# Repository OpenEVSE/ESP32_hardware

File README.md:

# ESP32_hardware
OpenEVSE network communications controllers based on the ESP32 Module.

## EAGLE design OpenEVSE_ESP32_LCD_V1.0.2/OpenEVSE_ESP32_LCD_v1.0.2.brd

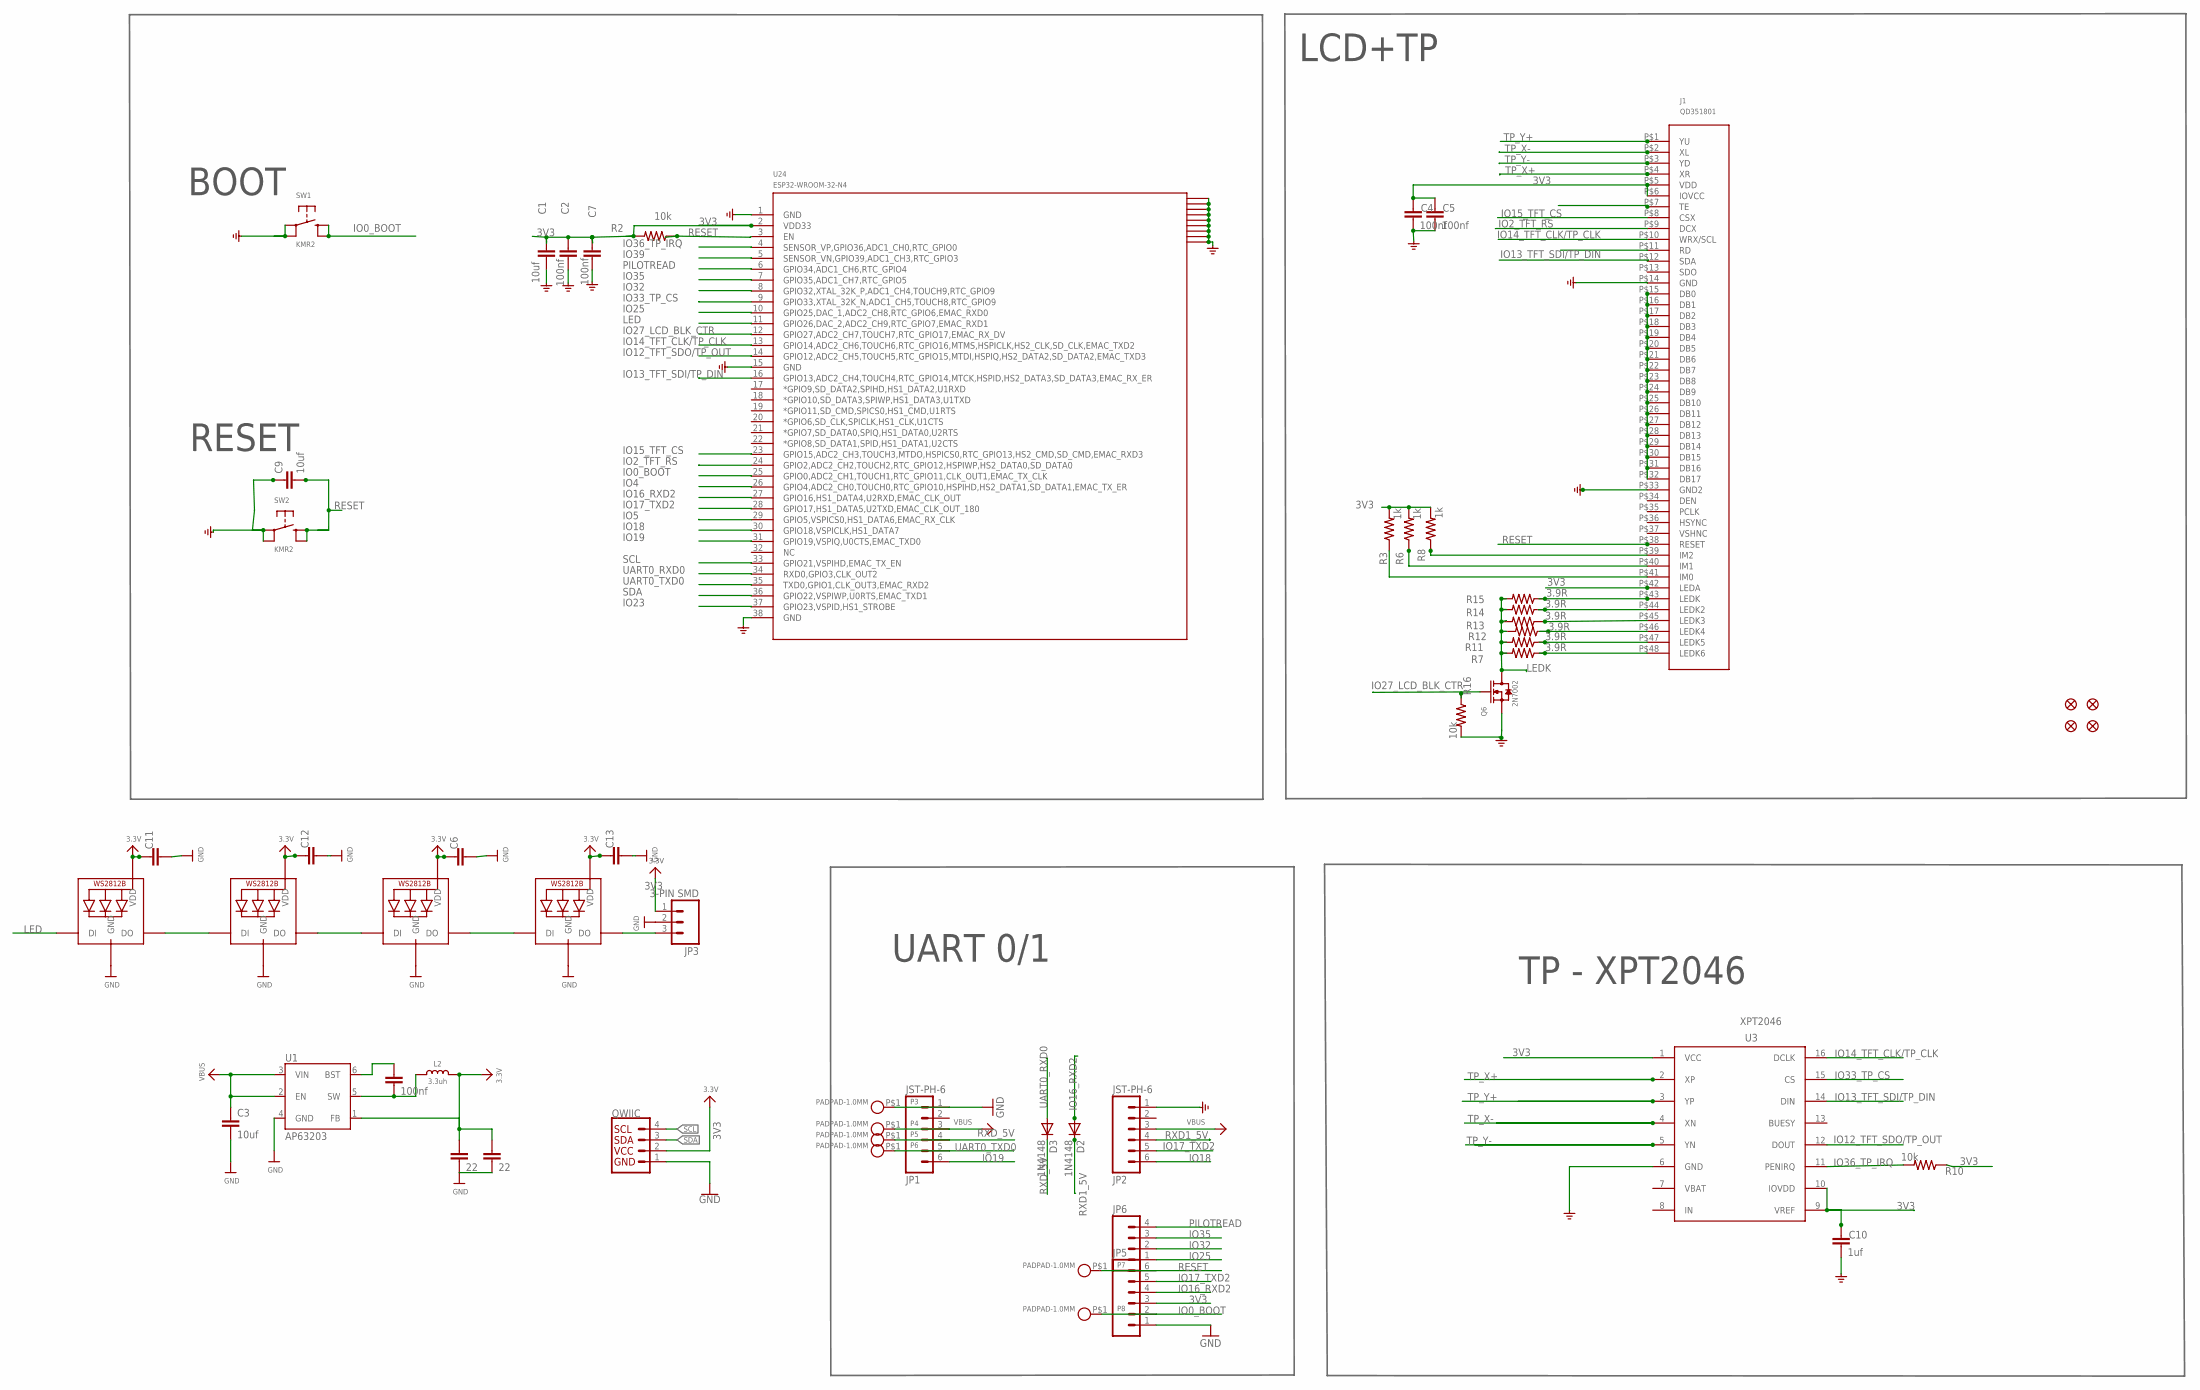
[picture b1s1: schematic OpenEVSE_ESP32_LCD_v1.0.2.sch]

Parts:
C1, C3, C9: 10uf; 0805
C2, C4, C5, C7, C14: 100nf; 0805
C6, C11, C12, C13: CAP0805; 0805
C8, C15: 22; 0805
C10: 1uf; 0805
D2, D3: 1N4148; SOD123
FID1, FID2, FID3, FID4: FIDUCIAL1X2.5; FIDUCIAL-1X2.5
J1: QD351801; QD351801-0.8MM*48
JP1, JP2: JST-PH-6
JP3: 3-PIN SMD; JST-3-SMD
JP5: M06SMD; 1X06-SMD
JP6: M04SMD; 1X04-SMD
L2: 3.3uh; MICROBUILDER_INDUCTOR_5X5MM_NR5040_NOTHERMALS
LED1, LED2, LED3, LED4: WS2812B3535; LED3535
P3, P4, P5, P6, P7, P8: PADPAD-1.0MM; PAD-1.0MM
Q6: 2N7002; SOT23
QWIIC: QWIIC_CONNECTORJS-1MM; JST04_1MM_RA
R2, R10, R16: 10k; 0805
R3, R6, R8: 1k; 0805
R7, R11, R12, R13, R14, R15: 3.9R; 0805
SW1, SW2: KMR2; BTN_KMR2_4.6X2.8
U1: AP63203; SOT23-6
U3: XP2046; XP2046-SSOP16
U24: ESP32-WROOM-32-N4

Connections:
3V3: C1.1, C2.1, C4.1, C5.1, C6.1, C7.1, C8.1, C10.1, C11.1, C12.1, C13.1, C15.1, J1.P$5 (VDD), J1.P$6 (IOVCC), J1.P$42 (LEDA), JP3.1, JP5.3, L2.P$2 (2), LED1.2 (VDD), LED2.2 (VDD), LED3.2 (VDD), LED4.2 (VDD), QWIIC.2, R2.2, R3.2, R6.2, R8.2, R10.1, U1.1 (FB), U3.1 (VCC), U3.9 (VREF), U3.10 (IOVDD), U24.2 (VDD33)
GND: C1.2, C2.2, C3.2, C4.2, C5.2, C6.2, C7.2, C8.2, C9.1, C10.2, C11.2, C12.2, C13.2, C15.2, J1.P$14 (GND), J1.P$33 (GND2), JP1.1, JP2.1, JP3.2, JP5.1, LED1.4 (GND), LED2.4 (GND), LED3.4 (GND), LED4.4 (GND), P3.P$1, Q6.2 (S), QWIIC.1, R16.2, SW1.A, SW1.A' (P1), SW2.A, SW2.A' (P1), U1.4 (GND), U3.6 (GND), U24.1 (GND), U24.15 (GND), U24.38 (GND), U24.41 (GND), U24.42 (GND), U24.43 (GND), U24.44 (GND), U24.45 (GND), U24.46 (GND), U24.47 (GND), U24.48 (GND), U24.49 (GND)
IO0_BOOT: JP5.2, P8.P$1, SW1.B (S), SW1.B' (S1), U24.25 (GPIO0,ADC2_CH1,TOUCH1,RTC_GPIO11,CLK_OU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)
IO2_TFT_RS: J1.P$9 (DCX), U24.24 (GPIO2,ADC2_CH2,TOUCH2,RTC_GPIO12,HSPIWP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)
IO4: U24.26 (GPIO4,ADC2_CH0,TOUCH0,RTC_GPIO10,HSPIHD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)
IO5: U24.29 (GPIO5,VSPICS0,HS1_DATA6,EMAC_RX_CLK)
IO12_TFT_SDO/TP_OUT: U3.12 (DOUT), U24.14 (GPIO12,ADC2_CH5,TOUCH5,RTC_GPIO15,MTDI,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)
IO13_TFT_SDI/TP_DIN: J1.P$12 (SDA), U3.14 (DIN), U24.16 (GPIO13,ADC2_CH4,TOUCH4,RTC_GPIO14,MTCK,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)
IO14_TFT_CLK/TP_CLK: J1.P$10 (WRX/SCL), U3.16 (DCLK), U24.13 (GPIO14,ADC2_CH6,TOUCH6,RTC_GPIO16,MTMS,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)
IO15_TFT_CS: J1.P$8 (CSX), U24.23 (GPIO15,ADC2_CH3,TOUCH3,MTDO,HSPICS0,RTC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)
IO16_RXD2: D2.A, JP5.4, U24.27 (GPIO16,HS1_DATA4,U2RXD,EMAC_CLK_OUT)
IO17_TXD2: JP2.5, JP5.5, U24.28 (GPIO17,HS1_DATA5,U2TXD,EMAC_CLK_OUT_180)
IO18: JP2.6, U24.30 (GPIO18,VSPICLK,HS1_DATA7)
IO19: JP1.6, U24.31 (GPIO19,VSPIQ,U0CTS,EMAC_TXD0)
IO23: U24.37 (GPIO23,VSPID,HS1_STROBE)
IO25: JP6.1, U24.10 (GPIO25,DAC_1,ADC2_CH8,RTC_GPIO6,EMAC_RX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)
IO27_LCD_BLK_CTR: Q6.1 (G), R16.1, U24.12 (GPIO27,ADC2_CH7,TOUCH7,RTC_GPIO17,EMAC_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)
IO32: JP6.2, U24.8 (GPIO32,XTAL_32K_P,ADC1_CH4,TOUCH9,RTC_G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)
IO33_TP_CS: U3.15 (CS), U24.9 (GPIO33,XTAL_32K_N,ADC1_CH5,TOUCH8,RTC_G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)
IO35: JP6.3, U24.7 (GPIO35,ADC1_CH7,RTC_GPIO5)
IO36_TP_IRQ: R10.2, U3.11 (PENIRQ), U24.4 (SENSOR_VP,GPIO36,ADC1_CH0,RTC_GPIO0)
IO39: U24.5 (SENSOR_VN,GPIO39,ADC1_CH3,RTC_GPIO3)
LED: LED1.1 (DI), U24.11 (GPIO26,DAC_2,ADC2_CH9,RTC_GPIO7,EMAC_RX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)
LEDK: Q6.3 (D), R7.2, R11.2, R12.2, R13.2, R14.2, R15.2
unnamed: LED1.3 (DO), LED2.1 (DI)
unnamed: J1.P$15 (DB0), J1.P$16 (DB1), J1.P$17 (DB2), J1.P$18 (DB3), J1.P$19 (DB4), J1.P$20 (DB5), J1.P$21 (DB6), J1.P$22 (DB7), J1.P$23 (DB8), J1.P$24 (DB9), J1.P$25 (DB10), J1.P$26 (DB11), J1.P$27 (DB12), J1.P$28 (DB13), J1.P$29 (DB14), J1.P$30 (DB15), J1.P$31 (DB16), J1.P$32 (DB17)
unnamed: LED3.3 (DO), LED4.1 (DI)
unnamed: C14.2, L2.P$1 (1), U1.5 (SW)
unnamed: J1.P$44 (LEDK2), R14.1
unnamed: LED2.3 (DO), LED3.1 (DI)
unnamed: J1.P$43 (LEDK), R15.1
unnamed: JP3.3, LED4.3 (DO)
unnamed: J1.P$39 (IM2), R8.1
unnamed: J1.P$40 (IM1), R6.1
unnamed: J1.P$41 (IM0), R3.1
unnamed: C14.1, U1.6 (BST)
unnamed: J1.P$45 (LEDK3), R13.1
unnamed: J1.P$46 (LEDK4), R12.1
unnamed: J1.P$47 (LEDK5), R11.1
unnamed: J1.P$48 (LEDK6), R7.1
PILOTREAD: JP6.4, U24.6 (GPIO34,ADC1_CH6,RTC_GPIO4)
RESET: C9.2, J1.P$38 (RESET), JP5.6, P7.P$1, R2.1, SW2.B (S), SW2.B' (S1), U24.3 (EN)
RXD1_5V: D2.C, JP2.4
RXD_5V: D3.C, JP1.4, P5.P$1
SCL: QWIIC.4, U24.33 (GPIO21,VSPIHD,EMAC_TX_EN)
SDA: QWIIC.3, U24.36 (GPIO22,VSPIWP,U0RTS,EMAC_TXD1)
TP_X+: J1.P$4 (XR), U3.2 (XP)
TP_X-: J1.P$2 (XL), U3.4 (XN)
TP_Y+: J1.P$1 (YU), U3.3 (YP)
TP_Y-: J1.P$3 (YD), U3.5 (YN)
UART0_RXD0: D3.A, U24.34 (RXD0,GPIO3,CLK_OUT2)
UART0_TXD0: JP1.5, P6.P$1, U24.35 (TXD0,GPIO1,CLK_OUT3,EMAC_RXD2)
VBUS: C3.1, JP1.3, JP2.3, P4.P$1, U1.2 (EN), U1.3 (VIN)

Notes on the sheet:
UART 0/1
BOOT
RESET
LCD+TP
TP - XPT2046

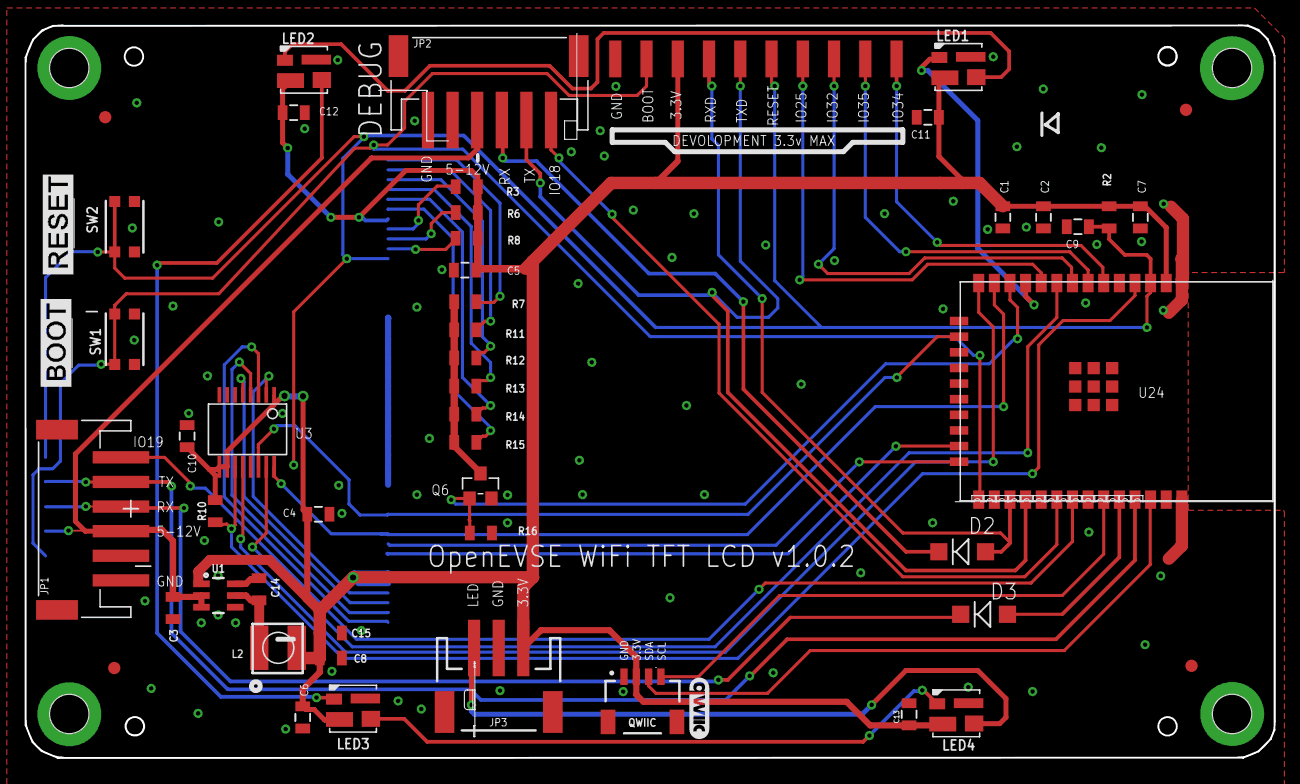
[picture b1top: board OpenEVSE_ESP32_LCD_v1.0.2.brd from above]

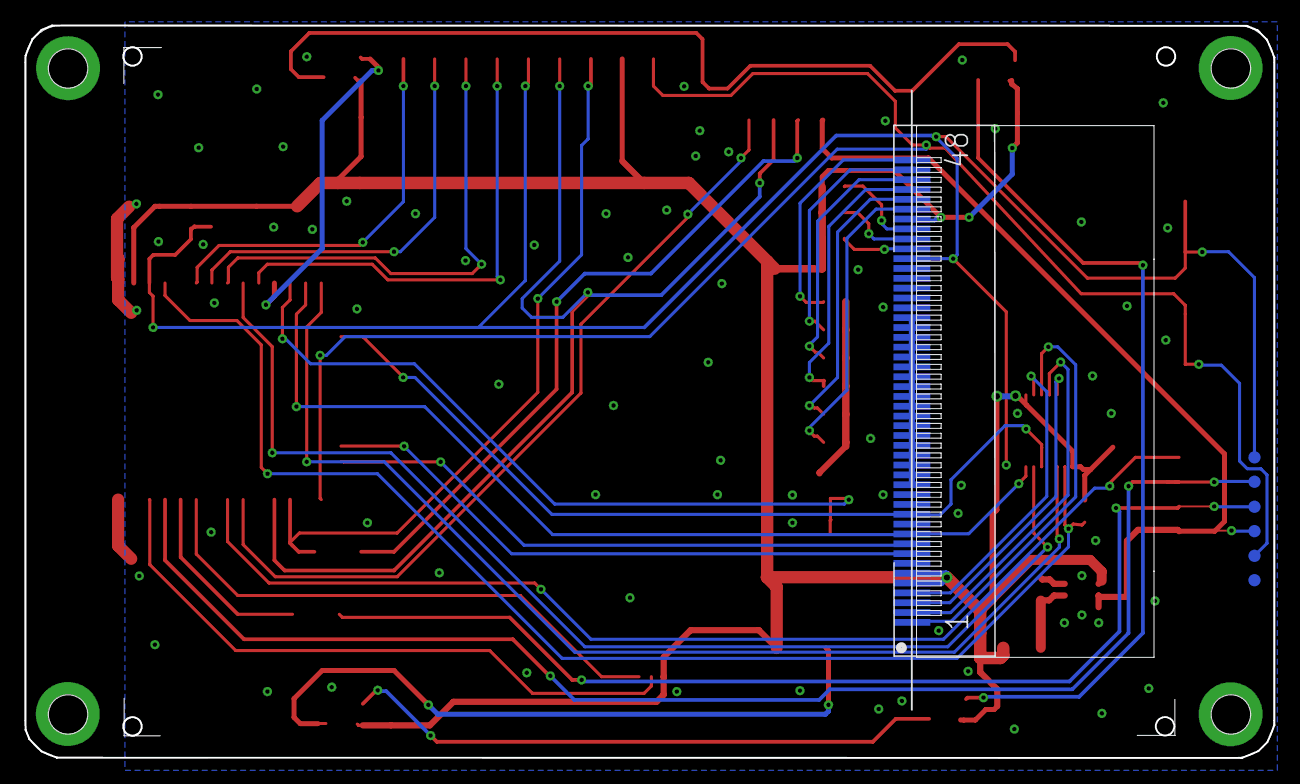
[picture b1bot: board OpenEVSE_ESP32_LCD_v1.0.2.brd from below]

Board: 2 copper layers, 101.5 x 59.5 mm, 59 parts (7 on the bottom side), 49 nets.

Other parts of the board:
U$2: 3.5底板框
U$44: QWIIC_5MM

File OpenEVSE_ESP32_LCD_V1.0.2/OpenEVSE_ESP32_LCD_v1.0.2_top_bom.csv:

Comment,Designator,Footprint,LCSC Part #
1N4148,C6 C11 C12 C13 JP5 JP6 QWIIC D2 D3,SOD123,
1k,R3 R6 R8,0805,
1uf,C10,0805,
2N7002,Q6,SOT23,
3-PIN SMD,JP3,JST-3-SMD,
3.3uh,L2,MICROBUILDER_INDUCTOR_5X5MM_NR5040_NOTHERMALS,
3.9R,R7 R11 R12 R13 R14 R15,0805,
4.7uf,C9,0805,
10k,R2 R10 R16,0805,
10uf,C1 C3,0805,
22,C8 C15,0805,
100nf,C2 C4 C5 C7 C14,0805,
AP63203,U1,SOT23-6,
ESP32-WROOM-32-N4,U24,ESP32-WROOM-32-N4,
FIDUCIAL1X2.5,FID1 FID2 FID3 FID4,FIDUCIAL-1X2.5,
JST-PH-6,JP1 JP2,JST-PH-6,
KMR2,SW1 SW2,BTN_KMR2_4.6X2.8,
WS2812B3535,LED1 LED2 LED3 LED4,LED3535,
XP2046,U3,XP2046-SSOP16,

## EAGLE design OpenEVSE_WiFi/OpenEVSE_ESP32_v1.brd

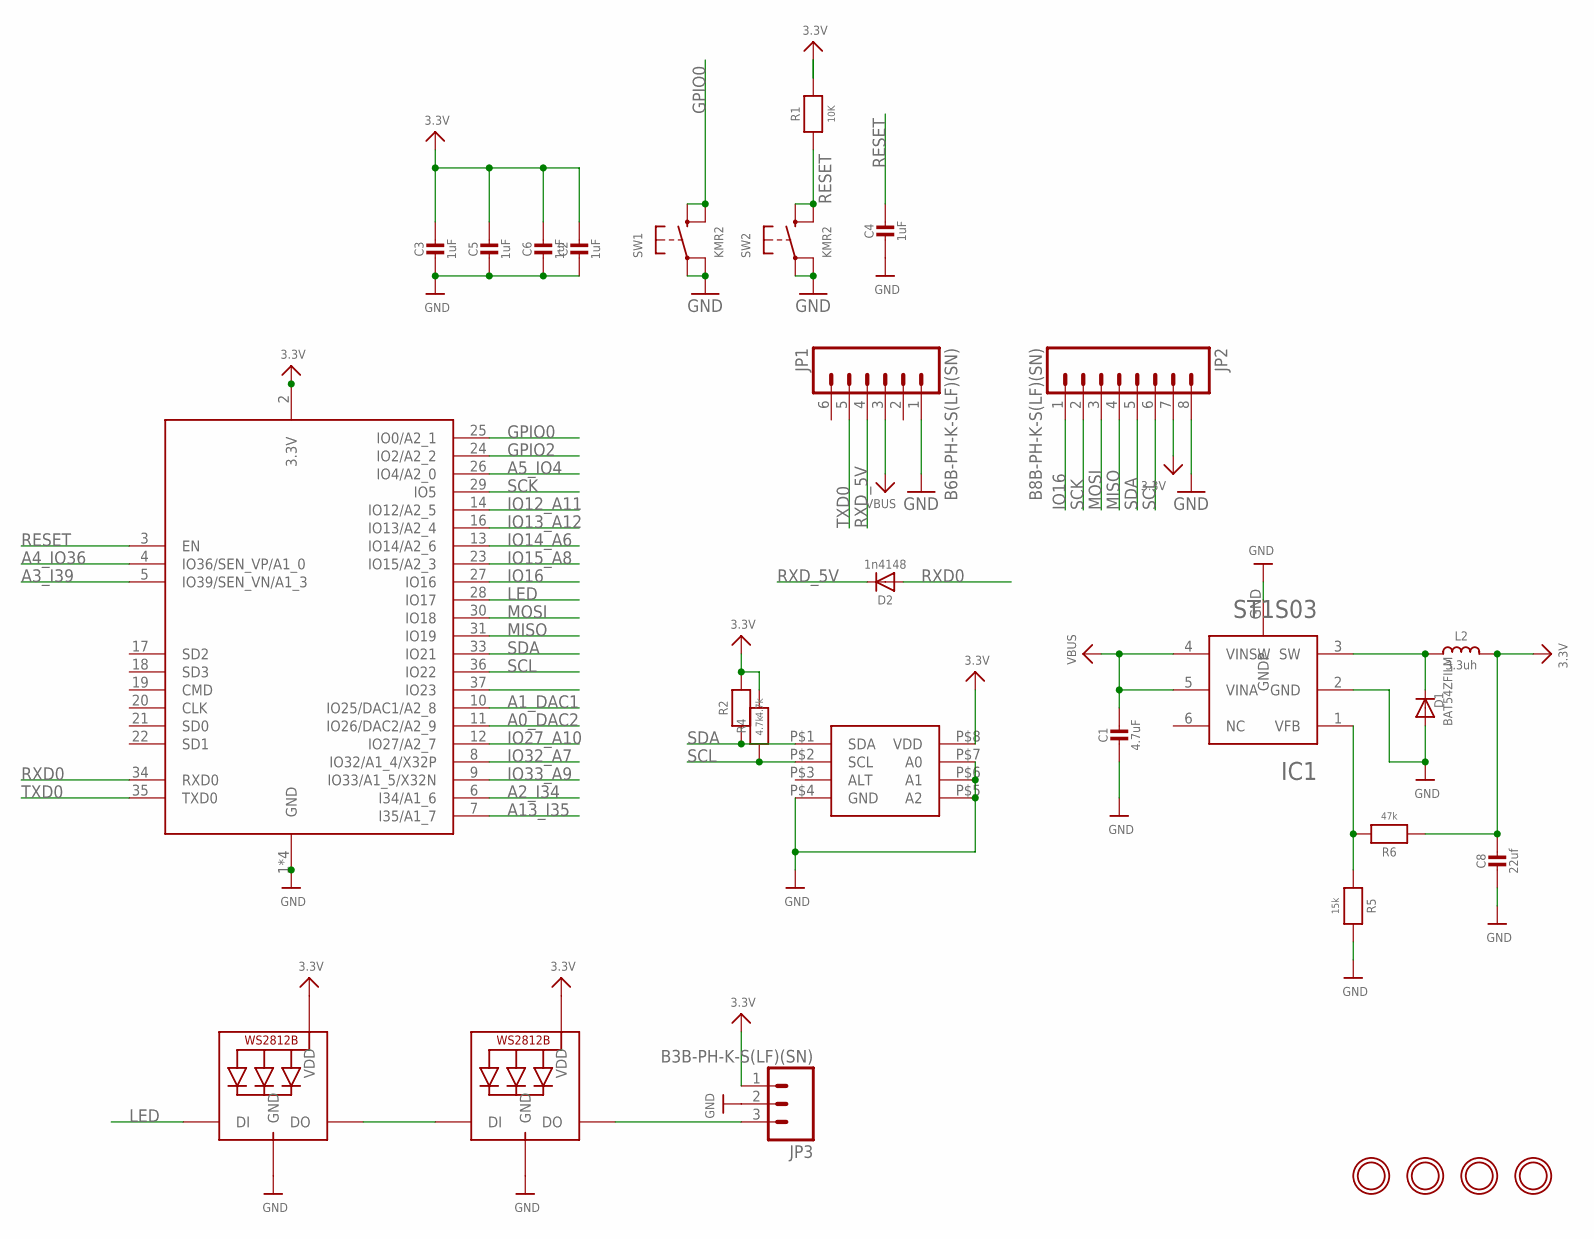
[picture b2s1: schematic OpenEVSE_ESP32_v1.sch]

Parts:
C1: 4.7uF; 0603-NO
C2, C3, C4, C5, C6: 1uF; 0603-NO
C8: 22uf; 0603-NO
D1: BAT54ZFILM; SOD-123
D2: 1n4148; SOD-323
IC1: ST1S03; DFQN6D
IC2: MCP9808; MSOP8
JP1: B6B-PH-K-S(LF)(SN); JST6
JP2: B8B-PH-K-S(LF)(SN); JST8
JP3: B3B-PH-K-S(LF)(SN); JST-3-PTH-VERT
L2: 3.3uh; MICROBUILDER_INDUCTOR_5X5MM_NR5040_NOTHERMALS
LED1, LED2: SK6812MINI; MICROBUILDER_LED3535
R1: 10K; 0603-NO
R2, R4: 4.7k; 0603-NO
R5: 15k; 0603-NO
R6: 47k; 0603-NO
SW1, SW2: KMR2; BTN_KMR2_4.6X2.8
U$8, U$17, U$25, U$27: MOUNTINGHOLE2.5; MOUNTINGHOLE_2.5_PLATED
X2: ESP32-WROOM-32; WROOM32_SKINNY

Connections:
3.3V: C2.1, C3.1, C5.1, C6.1, C8.1, IC2.P$8 (VDD), JP2.7, JP3.1, L2.P$2 (2), LED1.2 (VDD), LED2.2 (VDD), R1.2, R2.2, R4.2, R6.1, X2.2 (3.3V)
A0_DAC2: X2.11 (IO26/DAC2/A2_9)
A1_DAC1: X2.10 (IO25/DAC1/A2_8)
A2_I34: X2.6 (I34/A1_6)
A3_I39: X2.5 (IO39/SEN_VN/A1_3)
A4_IO36: X2.4 (IO36/SEN_VP/A1_0)
A5_IO4: X2.26 (IO4/A2_0)
A13_I35: X2.7 (I35/A1_7)
GND: C1.2, C2.2, C3.2, C4.2, C5.2, C6.2, C8.2, D1.A, IC1.2 (GND), IC1.GND (GNDP), IC2.P$4 (GND), IC2.P$5 (A2), IC2.P$6 (A1), IC2.P$7 (A0), JP1.1, JP2.8, JP3.2, LED1.4 (GND), LED2.4 (GND), R5.2, SW1.A, SW1.A' (P1), SW2.A, SW2.A' (P1), X2.1 (GND), X2.15 (GND), X2.38 (GND), X2.P$1 (GND)
GPIO0: SW1.B (S), SW1.B' (S1), X2.25 (IO0/A2_1)
GPIO2: X2.24 (IO2/A2_2)
IO12_A11: X2.14 (IO12/A2_5)
IO13_A12: X2.16 (IO13/A2_4)
IO14_A6: X2.13 (IO14/A2_6)
IO15_A8: X2.23 (IO15/A2_3)
IO16: JP2.1, X2.27 (IO16)
IO27_A10: X2.12 (IO27/A2_7)
IO32_A7: X2.8 (IO32/A1_4/X32P)
IO33_A9: X2.9 (IO33/A1_5/X32N)
LED: LED1.1 (DI), X2.28 (IO17)
MISO: JP2.4, X2.31 (IO19)
MOSI: JP2.3, X2.30 (IO18)
unnamed: JP3.3, LED2.3 (DO)
unnamed: LED1.3 (DO), LED2.1 (DI)
unnamed: IC1.1 (VFB), R5.1, R6.2
unnamed: D1.C, IC1.3 (SW), L2.P$1 (1)
RESET: C4.1, R1.1, SW2.B (S), SW2.B' (S1), X2.3 (EN)
RXD0: D2.A, X2.34 (RXD0)
RXD_5V: D2.C, JP1.4
SCK: JP2.2, X2.29 (IO5)
SCL: IC2.P$2 (SCL), JP2.6, R4.1, X2.36 (IO22)
SDA: IC2.P$1 (SDA), JP2.5, R2.1, X2.33 (IO21)
TXD0: JP1.5, X2.35 (TXD0)
VBUS: C1.1, IC1.4 (VINSW), IC1.5 (VINA), JP1.3

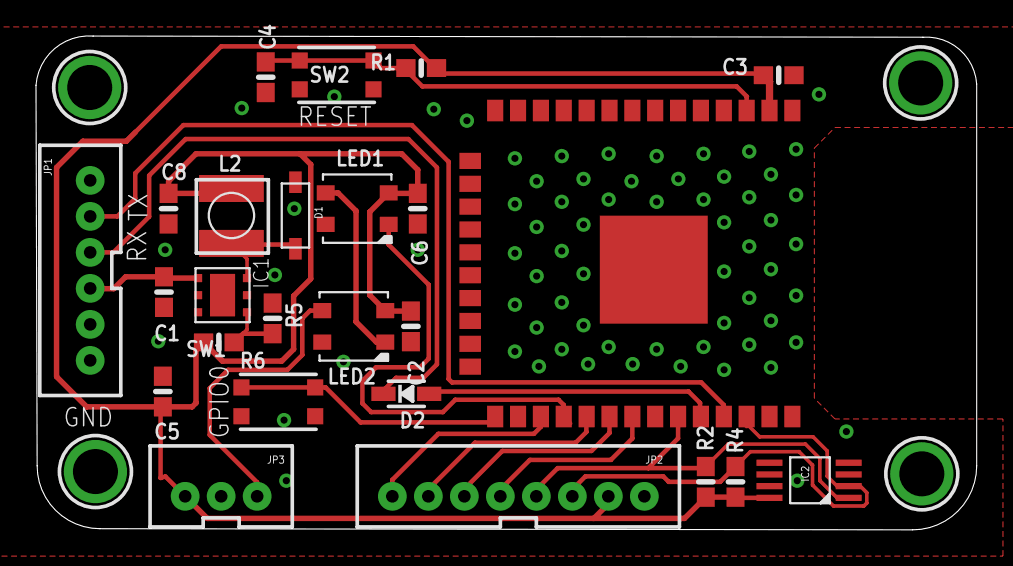
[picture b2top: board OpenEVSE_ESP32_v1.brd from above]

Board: 2 copper layers, 52.3 x 27.4 mm, 29 parts (0 on the bottom side), 19 nets.

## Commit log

2021-04-20 Add v1 source files
2021-04-29 Upload Board pinout
2021-04-29 JPG pinout
2021-04-29 Add image
2021-05-06 Upload Gerbers
    Upload GERBERS
2025-10-16 TFT LCD

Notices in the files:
parts and their libraries:
SparkFun-Connectors: Licensing: Creative Commons ShareAlike 4.0 International - https://creativecommons.org/licenses/by-sa/4.0
SparkFun: Licensing: CC v3.0 Share-Alike You are welcome to use this library for commercial purposes.
